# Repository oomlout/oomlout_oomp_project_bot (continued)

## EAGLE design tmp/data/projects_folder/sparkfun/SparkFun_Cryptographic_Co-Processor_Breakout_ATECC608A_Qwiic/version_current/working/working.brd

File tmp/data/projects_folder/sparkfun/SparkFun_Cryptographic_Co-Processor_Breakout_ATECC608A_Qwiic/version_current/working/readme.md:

# SparkFun_Cryptographic_Co-Processor_Breakout_ATECC608A_Qwiic by sparkfun  
This is a harvested standardized copy of a project from github.  
The original project can be found at:  
https://github.com/sparkfun/SparkFun_Cryptographic_Co-Processor_Breakout_ATECC608A_Qwiic  
Please consult that link for additional, details, files, and license information.  
Note: It was auto harvested and if the original repo had more than one board file or anything out of the ordinary the files here are likely not representative.

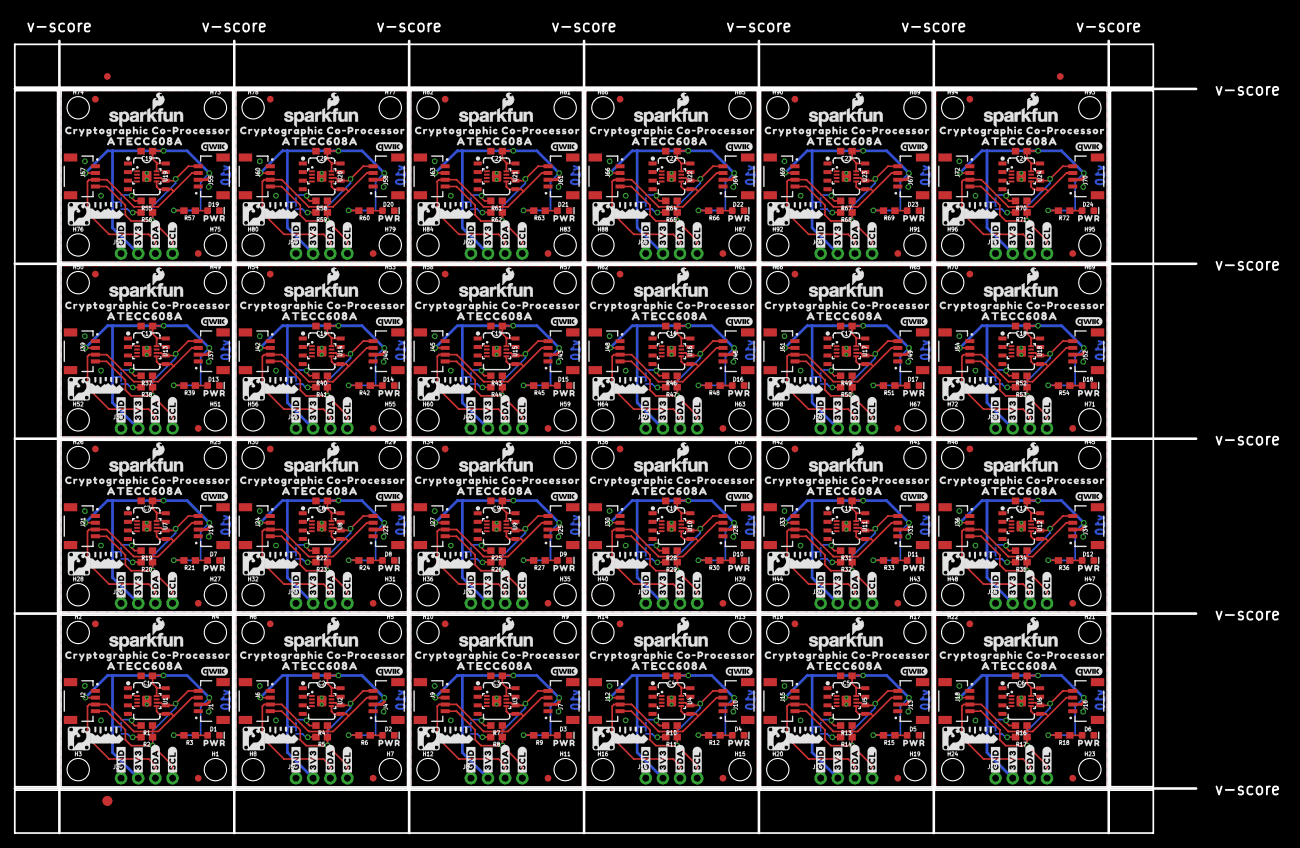
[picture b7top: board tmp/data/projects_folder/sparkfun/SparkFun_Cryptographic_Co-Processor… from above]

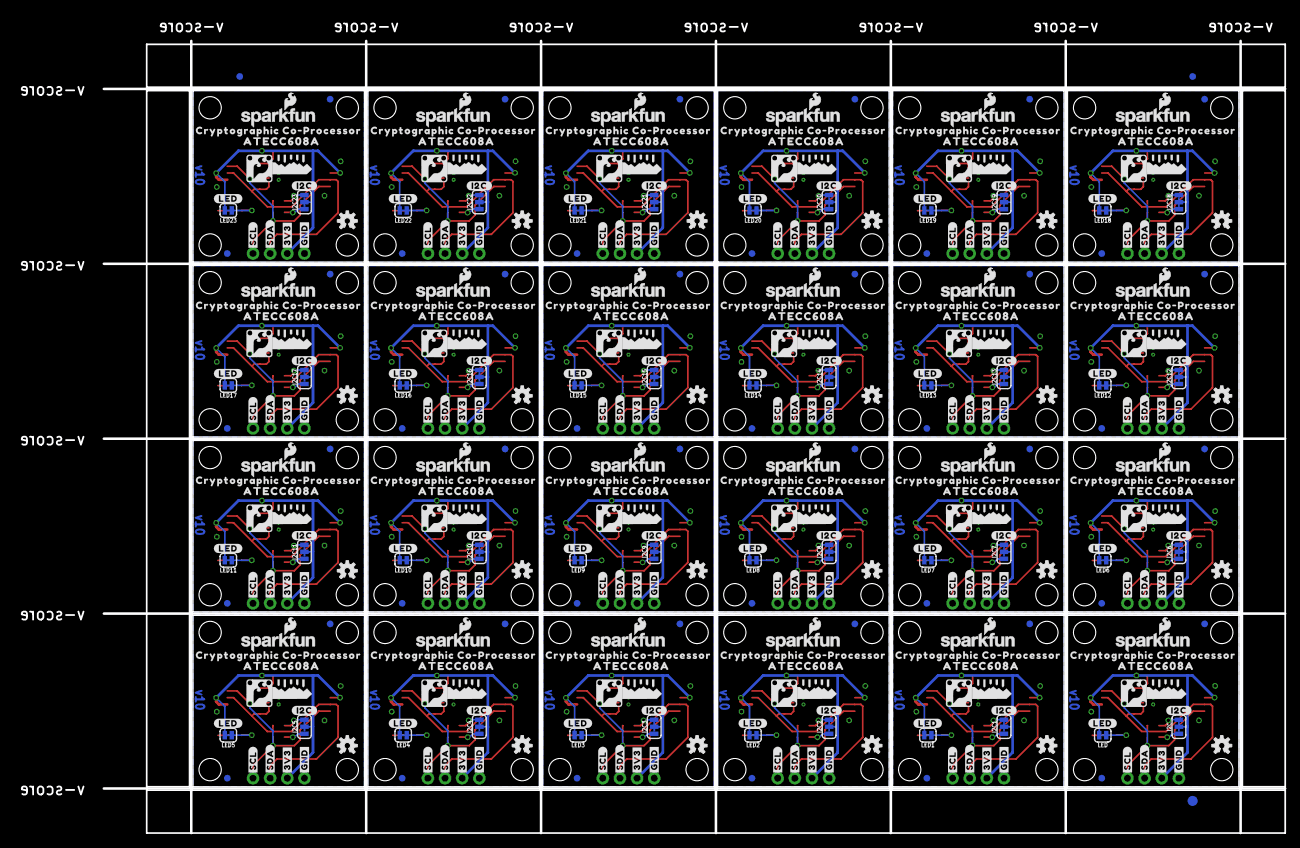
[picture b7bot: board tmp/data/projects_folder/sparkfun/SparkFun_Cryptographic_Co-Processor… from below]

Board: 2 copper layers, 175.0 x 117.3 mm, 966 parts (363 on the bottom side), 192 nets.

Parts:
C1, C2, C3, C4, C5, C6, C7, C8, C9, C10, C11, C12, C13, C14, C15, C16, C17, C18, C19, C20, C21, C22, C23, C24: 0.1uF; 0603
D1, D2, D3, D4, D5, D6, D7, D8, D9, D10, D11, D12, D13, D14, D15, D16, D17, D18, D19, D20, D21, D22, D23, D24: RED; LED-0603
E$1, E$2, E$3, E$4: FIDUCIAL-1X2
E$5, E$6: FIDUCIAL-1.5X3
FD1, FD2, FD3, FD4, FD5, FD6, FD7, FD8, FD9, FD10, FD11, FD12, FD13, FD14, FD15, FD16, FD17, FD18, FD19, FD20, FD21, FD22, FD23, FD24, FD25, FD26, FD27, FD28, FD29, FD30, FD31, FD32, FD33, FD34, FD35, FD36, FD37, FD38, FD39, FD40, FD41, FD42, FD43, FD44, FD45, FD46, FD47, FD48, FD49, FD50, FD51, FD52, FD53, FD54, FD55, FD56, FD57, FD58, FD59, FD60, FD61, FD62, FD63, FD64, FD65, FD66, FD67, FD68, FD69, FD70, FD71, FD72, FD73, FD74, FD75, FD76, FD77, FD78, FD79, FD80, FD81, FD82, FD83, FD84, FD85, FD86, FD87, FD88, FD89, FD90, FD91, FD92, FD93, FD94, FD95, FD96: FIDUCIAL1X2; FIDUCIAL-1X2
H1, H2, H3, H4, H5, H6, H7, H8, H9, H10, H11, H12, H13, H14, H15, H16, H17, H18, H19, H20, H21, H22, H23, H24, H25, H26, H27, H28, H29, H30, H31, H32, H33, H34, H35, H36, H37, H38, H39, H40, H41, H42, H43, H44, H45, H46, H47, H48, H49, H50, H51, H52, H53, H54, H55, H56, H57, H58, H59, H60, H61, H62, H63, H64, H65, H66, H67, H68, H69, H70, H71, H72, H73, H74, H75, H76, H77, H78, H79, H80, H81, H82, H83, H84, H85, H86, H87, H88, H89, H90, H91, H92, H93, H94, H95, H96: STAND-OFF
I2C, I2C1, I2C2, I2C3, I2C4, I2C5, I2C6, I2C7, I2C8, I2C9, I2C10, I2C11, I2C12, I2C13, I2C14, I2C15, I2C16, I2C17, I2C18, I2C19, I2C20, I2C21, I2C22, I2C23: SMT-JUMPER_3_2-NC_TRACE_SILK
J1, J2, J4, J6, J7, J9, J10, J12, J13, J15, J16, J18, J19, J21, J22, J24, J25, J27, J28, J30, J31, J33, J34, J36, J37, J39, J40, J42, J43, J45, J46, J48, J49, J51, J52, J54, J55, J57, J58, J60, J61, J63, J64, J66, J67, J69, J70, J72: QWIIC; JST04_1MM_RA
J3, J5, J8, J11, J14, J17, J20, J23, J26, J29, J32, J35, J38, J41, J44, J47, J50, J53, J56, J59, J62, J65, J68, J71: PTH; 1X04_NO_SILK
LED, LED1, LED2, LED3, LED4, LED5, LED6, LED7, LED8, LED9, LED10, LED11, LED12, LED13, LED14, LED15, LED16, LED17, LED18, LED19, LED20, LED21, LED22, LED23: SMT-JUMPER_2_NC_TRACE_SILK
LOGO1, LOGO2, LOGO6, LOGO7, LOGO10, LOGO11, LOGO14, LOGO15, LOGO18, LOGO19, LOGO22, LOGO23, LOGO26, LOGO27, LOGO30, LOGO31, LOGO34, LOGO35, LOGO38, LOGO39, LOGO42, LOGO43, LOGO46, LOGO47, LOGO50, LOGO51, LOGO54, LOGO55, LOGO58, LOGO59, LOGO62, LOGO63, LOGO66, LOGO67, LOGO70, LOGO71, LOGO74, LOGO75, LOGO78, LOGO79, LOGO82, LOGO83, LOGO86, LOGO87, LOGO90, LOGO91, LOGO94, LOGO95: SFE_LOGO_NAME_FLAME.1_INCH; SFE_LOGO_NAME_FLAME_.1
LOGO3, LOGO8, LOGO12, LOGO16, LOGO20, LOGO24, LOGO28, LOGO32, LOGO36, LOGO40, LOGO44, LOGO48, LOGO52, LOGO56, LOGO60, LOGO64, LOGO68, LOGO72, LOGO76, LOGO80, LOGO84, LOGO88, LOGO92, LOGO96: QWIIC_LOGO_4MM; QWIIC_4MM
LOGO4, LOGO5, LOGO9, LOGO13, LOGO17, LOGO21, LOGO25, LOGO29, LOGO33, LOGO37, LOGO41, LOGO45, LOGO49, LOGO53, LOGO57, LOGO61, LOGO65, LOGO69, LOGO73, LOGO77, LOGO81, LOGO85, LOGO89, LOGO93: OSHW-LOGOS; OSHW-LOGO-S
R1, R2, R4, R5, R7, R8, R10, R11, R13, R14, R16, R17, R19, R20, R22, R23, R25, R26, R28, R29, R31, R32, R34, R35, R37, R38, R40, R41, R43, R44, R46, R47, R49, R50, R52, R53, R55, R56, R58, R59, R61, R62, R64, R65, R67, R68, R70, R71: 4.7k; 0603
R3, R6, R9, R12, R15, R18, R21, R24, R27, R30, R33, R36, R39, R42, R45, R48, R51, R54, R57, R60, R63, R66, R69, R72: 1k; 0603
U1, U2, U3, U4, U5, U6, U7, U8, U9, U10, U11, U12, U13, U14, U15, U16, U17, U18, U19, U20, U21, U22, U23, U24: ATECC608A; DUAL_UDFN_2X3MM_SOIC-8
U$1, U$29, U$46, U$63, U$80, U$97, U$114, U$131, U$148, U$165, U$182, U$199, U$216, U$233, U$250, U$267, U$284, U$301, U$318, U$335, U$352, U$369, U$386, U$403: #I2C#0
U$2, U$13, U$15, U$24, U$37, U$41, U$54, U$58, U$71, U$75, U$88, U$92, U$105, U$109, U$122, U$126, U$139, U$143, U$156, U$160, U$173, U$177, U$190, U$194, U$207, U$211, U$224, U$228, U$241, U$245, U$258, U$262, U$275, U$279, U$292, U$296, U$309, U$313, U$326, U$330, U$343, U$347, U$360, U$364, U$377, U$381, U$394, U$398: #SCL#0
U$3, U$28, U$45, U$62, U$79, U$96, U$113, U$130, U$147, U$164, U$181, U$198, U$215, U$232, U$249, U$266, U$283, U$300, U$317, U$334, U$351, U$368, U$385, U$402: #LED#0
U$4, U$16, U$17, U$25, U$38, U$42, U$55, U$59, U$72, U$76, U$89, U$93, U$106, U$110, U$123, U$127, U$140, U$144, U$157, U$161, U$174, U$178, U$191, U$195, U$208, U$212, U$225, U$229, U$242, U$246, U$259, U$263, U$276, U$280, U$293, U$297, U$310, U$314, U$327, U$331, U$344, U$348, U$361, U$365, U$378, U$382, U$395, U$399: #SDA#0
U$5, U$7, U$30, U$31, U$47, U$48, U$64, U$65, U$81, U$82, U$98, U$99, U$115, U$116, U$132, U$133, U$149, U$150, U$166, U$167, U$183, U$184, U$200, U$201, U$217, U$218, U$234, U$235, U$251, U$252, U$268, U$269, U$285, U$286, U$302, U$303, U$319, U$320, U$336, U$337, U$353, U$354, U$370, U$371, U$387, U$388, U$404, U$405: ATECC608A0
U$6, U$18, U$20, U$26, U$39, U$43, U$56, U$60, U$73, U$77, U$90, U$94, U$107, U$111, U$124, U$128, U$141, U$145, U$158, U$162, U$175, U$179, U$192, U$196, U$209, U$213, U$226, U$230, U$243, U$247, U$260, U$264, U$277, U$281, U$294, U$298, U$311, U$315, U$328, U$332, U$345, U$349, U$362, U$366, U$379, U$383, U$396, U$400: #3V3#0
U$8, U$32, U$49, U$66, U$83, U$100, U$117, U$134, U$151, U$168, U$185, U$202, U$219, U$236, U$253, U$270, U$287, U$304, U$321, U$338, U$355, U$372, U$389, U$406: CRYPTO_COPROCESSOR_LOGO_LARGE
U$9, U$12, U$14, U$19, U$35, U$36, U$52, U$53, U$69, U$70, U$86, U$87, U$103, U$104, U$120, U$121, U$137, U$138, U$154, U$155, U$171, U$172, U$188, U$189, U$205, U$206, U$222, U$223, U$239, U$240, U$256, U$257, U$273, U$274, U$290, U$291, U$307, U$308, U$324, U$325, U$341, U$342, U$358, U$359, U$375, U$376, U$392, U$393: CRYPTOGRAPHIC_CO#PROCESSOR0
U$10, U$33, U$50, U$67, U$84, U$101, U$118, U$135, U$152, U$169, U$186, U$203, U$220, U$237, U$254, U$271, U$288, U$305, U$322, U$339, U$356, U$373, U$390, U$407: CRYPTO_COPROCESSOR_LOGO_SMALL
U$11, U$34, U$51, U$68, U$85, U$102, U$119, U$136, U$153, U$170, U$187, U$204, U$221, U$238, U$255, U$272, U$289, U$306, U$323, U$340, U$357, U$374, U$391, U$408: PWR0
U$21, U$22, U$23, U$27, U$40, U$44, U$57, U$61, U$74, U$78, U$91, U$95, U$108, U$112, U$125, U$129, U$142, U$146, U$159, U$163, U$176, U$180, U$193, U$197, U$210, U$214, U$227, U$231, U$244, U$248, U$261, U$265, U$278, U$282, U$295, U$299, U$312, U$316, U$329, U$333, U$346, U$350, U$363, U$367, U$380, U$384, U$397, U$401: #GND#0

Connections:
3.3V: C1.1, I2C.2, J1.2, J2.2, J3.2, LED.2, U1.8, U1.8S
3.3V1: C2.1, I2C1.2, J4.2, J5.2, J6.2, LED1.2, U2.8, U2.8S
3.3V2: C3.1, I2C2.2, J7.2, J8.2, J9.2, LED2.2, U3.8, U3.8S
3.3V3: C4.1, I2C3.2, J10.2, J11.2, J12.2, LED3.2, U4.8, U4.8S
3.3V4: C5.1, I2C4.2, J13.2, J14.2, J15.2, LED4.2, U5.8, U5.8S
3.3V5: C6.1, I2C5.2, J16.2, J17.2, J18.2, LED5.2, U6.8, U6.8S
3.3V6: C7.1, I2C6.2, J19.2, J20.2, J21.2, LED6.2, U7.8, U7.8S
3.3V7: C8.1, I2C7.2, J22.2, J23.2, J24.2, LED7.2, U8.8, U8.8S
3.3V8: C9.1, I2C8.2, J25.2, J26.2, J27.2, LED8.2, U9.8, U9.8S
3.3V9: C10.1, I2C9.2, J28.2, J29.2, J30.2, LED9.2, U10.8, U10.8S
3.3V10: C11.1, I2C10.2, J31.2, J32.2, J33.2, LED10.2, U11.8, U11.8S
3.3V11: C12.1, I2C11.2, J34.2, J35.2, J36.2, LED11.2, U12.8, U12.8S
3.3V12: C13.1, I2C12.2, J37.2, J38.2, J39.2, LED12.2, U13.8, U13.8S
3.3V13: C14.1, I2C13.2, J40.2, J41.2, J42.2, LED13.2, U14.8, U14.8S
3.3V14: C15.1, I2C14.2, J43.2, J44.2, J45.2, LED14.2, U15.8, U15.8S
3.3V15: C16.1, I2C15.2, J46.2, J47.2, J48.2, LED15.2, U16.8, U16.8S
3.3V16: C17.1, I2C16.2, J49.2, J50.2, J51.2, LED16.2, U17.8, U17.8S
3.3V17: C18.1, I2C17.2, J52.2, J53.2, J54.2, LED17.2, U18.8, U18.8S
3.3V18: C19.1, I2C18.2, J55.2, J56.2, J57.2, LED18.2, U19.8, U19.8S
3.3V19: C20.1, I2C19.2, J58.2, J59.2, J60.2, LED19.2, U20.8, U20.8S
3.3V20: C21.1, I2C20.2, J61.2, J62.2, J63.2, LED20.2, U21.8, U21.8S
3.3V21: C22.1, I2C21.2, J64.2, J65.2, J66.2, LED21.2, U22.8, U22.8S
3.3V22: C23.1, I2C22.2, J67.2, J68.2, J69.2, LED22.2, U23.8, U23.8S
3.3V23: C24.1, I2C23.2, J70.2, J71.2, J72.2, LED23.2, U24.8, U24.8S
GND: C1.2, D1.C, J1.1, J2.1, J3.1, U1.4, U1.4S, U1.P
GND1: C2.2, D2.C, J4.1, J5.1, J6.1, U2.4, U2.4S, U2.P
GND2: C3.2, D3.C, J7.1, J8.1, J9.1, U3.4, U3.4S, U3.P
GND3: C4.2, D4.C, J10.1, J11.1, J12.1, U4.4, U4.4S, U4.P
GND4: C5.2, D5.C, J13.1, J14.1, J15.1, U5.4, U5.4S, U5.P
GND5: C6.2, D6.C, J16.1, J17.1, J18.1, U6.4, U6.4S, U6.P
GND6: C7.2, D7.C, J19.1, J20.1, J21.1, U7.4, U7.4S, U7.P
GND7: C8.2, D8.C, J22.1, J23.1, J24.1, U8.4, U8.4S, U8.P
GND8: C9.2, D9.C, J25.1, J26.1, J27.1, U9.4, U9.4S, U9.P
GND9: C10.2, D10.C, J28.1, J29.1, J30.1, U10.4, U10.4S, U10.P
GND10: C11.2, D11.C, J31.1, J32.1, J33.1, U11.4, U11.4S, U11.P
GND11: C12.2, D12.C, J34.1, J35.1, J36.1, U12.4, U12.4S, U12.P
GND12: C13.2, D13.C, J37.1, J38.1, J39.1, U13.4, U13.4S, U13.P
GND13: C14.2, D14.C, J40.1, J41.1, J42.1, U14.4, U14.4S, U14.P
GND14: C15.2, D15.C, J43.1, J44.1, J45.1, U15.4, U15.4S, U15.P
GND15: C16.2, D16.C, J46.1, J47.1, J48.1, U16.4, U16.4S, U16.P
GND16: C17.2, D17.C, J49.1, J50.1, J51.1, U17.4, U17.4S, U17.P
GND17: C18.2, D18.C, J52.1, J53.1, J54.1, U18.4, U18.4S, U18.P
GND18: C19.2, D19.C, J55.1, J56.1, J57.1, U19.4, U19.4S, U19.P
GND19: C20.2, D20.C, J58.1, J59.1, J60.1, U20.4, U20.4S, U20.P
GND20: C21.2, D21.C, J61.1, J62.1, J63.1, U21.4, U21.4S, U21.P
GND21: C22.2, D22.C, J64.1, J65.1, J66.1, U22.4, U22.4S, U22.P
GND22: C23.2, D23.C, J67.1, J68.1, J69.1, U23.4, U23.4S, U23.P
GND23: C24.2, D24.C, J70.1, J71.1, J72.1, U24.4, U24.4S, U24.P
unnamed: I2C1.3, R4.2
unnamed: I2C1.1, R5.2
unnamed: D1.A, R3.1
unnamed: I2C.3, R1.2
unnamed: I2C.1, R2.2
unnamed: D2.A, R6.1
unnamed: LED.1, R3.2
unnamed: LED1.1, R6.2
unnamed: I2C2.3, R7.2
unnamed: I2C2.1, R8.2
unnamed: D3.A, R9.1
unnamed: LED2.1, R9.2
unnamed: I2C3.3, R10.2
unnamed: I2C3.1, R11.2
unnamed: D4.A, R12.1
unnamed: LED3.1, R12.2
unnamed: I2C4.3, R13.2
unnamed: I2C4.1, R14.2
unnamed: D5.A, R15.1
unnamed: LED4.1, R15.2
unnamed: I2C5.3, R16.2
unnamed: I2C5.1, R17.2
unnamed: D6.A, R18.1
unnamed: LED5.1, R18.2
unnamed: I2C6.3, R19.2
unnamed: I2C6.1, R20.2
unnamed: D7.A, R21.1
unnamed: LED6.1, R21.2
unnamed: I2C7.3, R22.2
unnamed: I2C7.1, R23.2
unnamed: D8.A, R24.1
unnamed: LED7.1, R24.2
unnamed: I2C8.3, R25.2
unnamed: I2C8.1, R26.2
unnamed: D9.A, R27.1
unnamed: LED8.1, R27.2
unnamed: I2C9.3, R28.2
unnamed: I2C9.1, R29.2
unnamed: D10.A, R30.1
unnamed: LED9.1, R30.2
unnamed: I2C10.3, R31.2
unnamed: I2C10.1, R32.2
unnamed: D11.A, R33.1
unnamed: LED10.1, R33.2
unnamed: I2C11.3, R34.2
unnamed: I2C11.1, R35.2
unnamed: D12.A, R36.1
unnamed: LED11.1, R36.2
unnamed: I2C12.3, R37.2
unnamed: I2C12.1, R38.2
unnamed: D13.A, R39.1
unnamed: LED12.1, R39.2
unnamed: I2C13.3, R40.2
unnamed: I2C13.1, R41.2
unnamed: D14.A, R42.1
unnamed: LED13.1, R42.2
unnamed: I2C14.3, R43.2
unnamed: I2C14.1, R44.2
unnamed: D15.A, R45.1
unnamed: LED14.1, R45.2
unnamed: I2C15.3, R46.2
unnamed: I2C15.1, R47.2
unnamed: D16.A, R48.1
unnamed: LED15.1, R48.2
unnamed: I2C16.3, R49.2
unnamed: I2C16.1, R50.2
unnamed: D17.A, R51.1
unnamed: LED16.1, R51.2
unnamed: I2C17.3, R52.2
unnamed: I2C17.1, R53.2
unnamed: D18.A, R54.1
unnamed: LED17.1, R54.2
unnamed: I2C18.3, R55.2
unnamed: I2C18.1, R56.2
unnamed: D19.A, R57.1
unnamed: LED18.1, R57.2
unnamed: I2C19.3, R58.2
unnamed: I2C19.1, R59.2
unnamed: D20.A, R60.1
unnamed: LED19.1, R60.2
unnamed: I2C20.3, R61.2
unnamed: I2C20.1, R62.2
unnamed: D21.A, R63.1
unnamed: LED20.1, R63.2
unnamed: I2C21.3, R64.2
unnamed: I2C21.1, R65.2
unnamed: D22.A, R66.1
unnamed: LED21.1, R66.2
unnamed: I2C22.3, R67.2
unnamed: I2C22.1, R68.2
unnamed: D23.A, R69.1
unnamed: LED22.1, R69.2
unnamed: I2C23.3, R70.2
unnamed: I2C23.1, R71.2
unnamed: D24.A, R72.1
unnamed: LED23.1, R72.2
SCL: J1.4, J2.4, J3.4, R2.1, U1.6, U1.6S
SCL1: J4.4, J5.4, J6.4, R5.1, U2.6, U2.6S
SCL2: J7.4, J8.4, J9.4, R8.1, U3.6, U3.6S
SCL3: J10.4, J11.4, J12.4, R11.1, U4.6, U4.6S
SCL4: J13.4, J14.4, J15.4, R14.1, U5.6, U5.6S
SCL5: J16.4, J17.4, J18.4, R17.1, U6.6, U6.6S
SCL6: J19.4, J20.4, J21.4, R20.1, U7.6, U7.6S
SCL7: J22.4, J23.4, J24.4, R23.1, U8.6, U8.6S
SCL8: J25.4, J26.4, J27.4, R26.1, U9.6, U9.6S
SCL9: J28.4, J29.4, J30.4, R29.1, U10.6, U10.6S
SCL10: J31.4, J32.4, J33.4, R32.1, U11.6, U11.6S
SCL11: J34.4, J35.4, J36.4, R35.1, U12.6, U12.6S
SCL12: J37.4, J38.4, J39.4, R38.1, U13.6, U13.6S
SCL13: J40.4, J41.4, J42.4, R41.1, U14.6, U14.6S
SCL14: J43.4, J44.4, J45.4, R44.1, U15.6, U15.6S
SCL15: J46.4, J47.4, J48.4, R47.1, U16.6, U16.6S
SCL16: J49.4, J50.4, J51.4, R50.1, U17.6, U17.6S
SCL17: J52.4, J53.4, J54.4, R53.1, U18.6, U18.6S
SCL18: J55.4, J56.4, J57.4, R56.1, U19.6, U19.6S
SCL19: J58.4, J59.4, J60.4, R59.1, U20.6, U20.6S
SCL20: J61.4, J62.4, J63.4, R62.1, U21.6, U21.6S
SCL21: J64.4, J65.4, J66.4, R65.1, U22.6, U22.6S
SCL22: J67.4, J68.4, J69.4, R68.1, U23.6, U23.6S
SCL23: J70.4, J71.4, J72.4, R71.1, U24.6, U24.6S
SDA: J1.3, J2.3, J3.3, R1.1, U1.5, U1.5S
SDA1: J4.3, J5.3, J6.3, R4.1, U2.5, U2.5S
SDA2: J7.3, J8.3, J9.3, R7.1, U3.5, U3.5S
SDA3: J10.3, J11.3, J12.3, R10.1, U4.5, U4.5S
SDA4: J13.3, J14.3, J15.3, R13.1, U5.5, U5.5S
SDA5: J16.3, J17.3, J18.3, R16.1, U6.5, U6.5S
SDA6: J19.3, J20.3, J21.3, R19.1, U7.5, U7.5S
SDA7: J22.3, J23.3, J24.3, R22.1, U8.5, U8.5S
SDA8: J25.3, J26.3, J27.3, R25.1, U9.5, U9.5S
SDA9: J28.3, J29.3, J30.3, R28.1, U10.5, U10.5S
SDA10: J31.3, J32.3, J33.3, R31.1, U11.5, U11.5S
SDA11: J34.3, J35.3, J36.3, R34.1, U12.5, U12.5S
SDA12: J37.3, J38.3, J39.3, R37.1, U13.5, U13.5S
SDA13: J40.3, J41.3, J42.3, R40.1, U14.5, U14.5S
SDA14: J43.3, J44.3, J45.3, R43.1, U15.5, U15.5S
SDA15: J46.3, J47.3, J48.3, R46.1, U16.5, U16.5S
SDA16: J49.3, J50.3, J51.3, R49.1, U17.5, U17.5S
SDA17: J52.3, J53.3, J54.3, R52.1, U18.5, U18.5S
SDA18: J55.3, J56.3, J57.3, R55.1, U19.5, U19.5S
SDA19: J58.3, J59.3, J60.3, R58.1, U20.5, U20.5S
SDA20: J61.3, J62.3, J63.3, R61.1, U21.5, U21.5S
SDA21: J64.3, J65.3, J66.3, R64.1, U22.5, U22.5S
SDA22: J67.3, J68.3, J69.3, R67.1, U23.5, U23.5S
SDA23: J70.3, J71.3, J72.3, R70.1, U24.5, U24.5S

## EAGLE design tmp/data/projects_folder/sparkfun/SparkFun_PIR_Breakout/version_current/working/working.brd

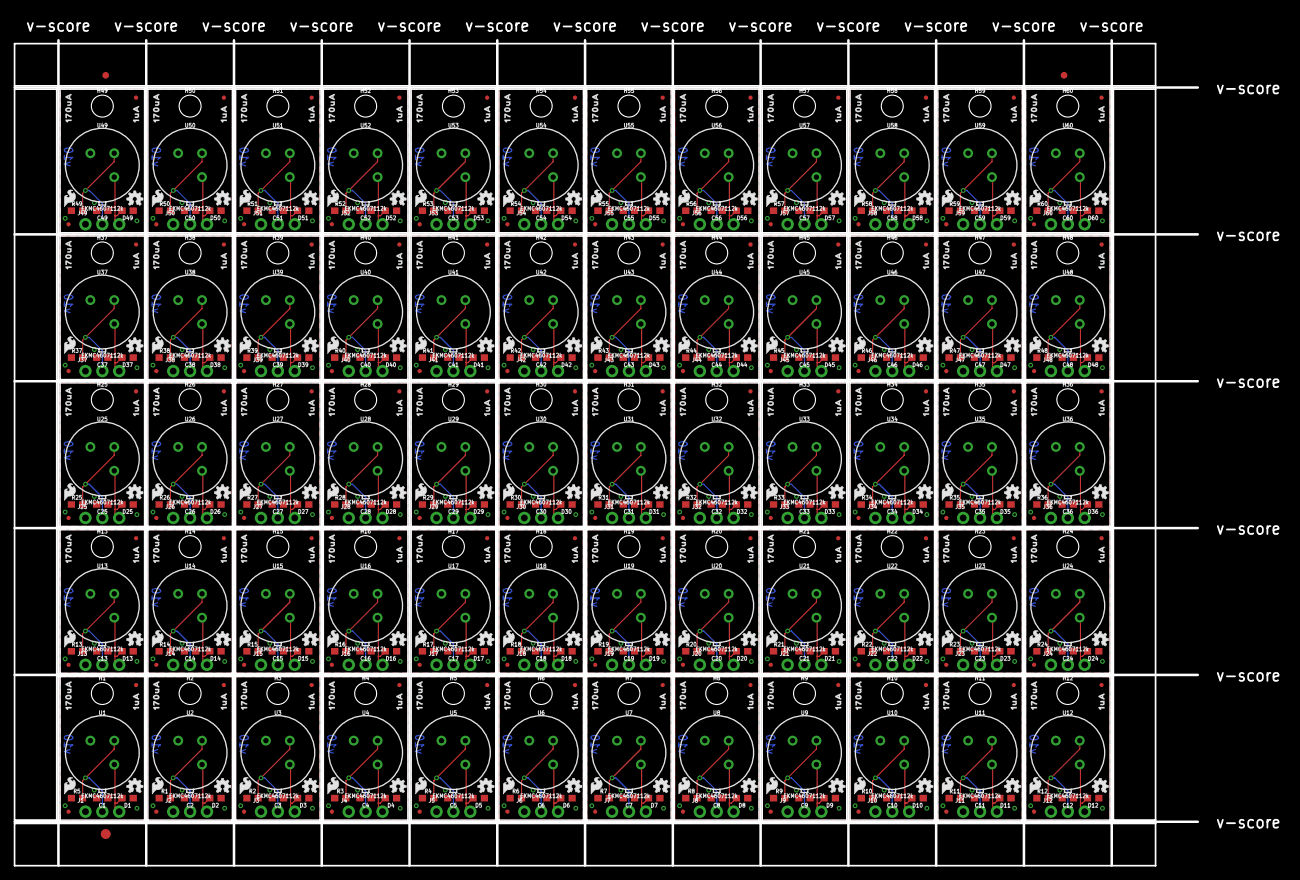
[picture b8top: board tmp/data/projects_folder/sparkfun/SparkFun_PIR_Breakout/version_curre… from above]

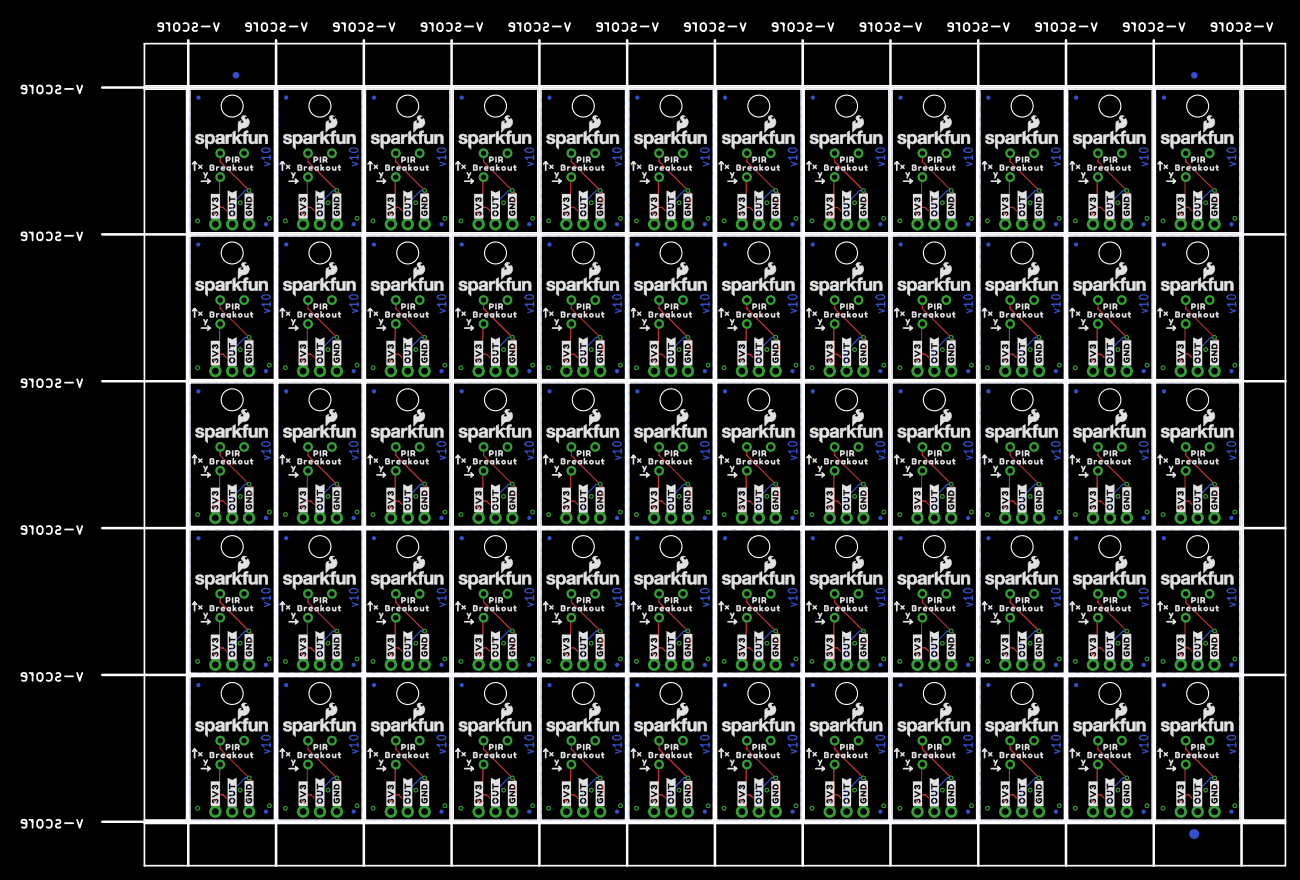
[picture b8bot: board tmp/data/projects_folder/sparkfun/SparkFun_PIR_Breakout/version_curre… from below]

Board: 2 copper layers, 178.1 x 124.2 mm, 1326 parts (603 on the bottom side), 180 nets.

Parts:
C1, C2, C3, C4, C5, C6, C7, C8, C9, C10, C11, C12, C13, C14, C15, C16, C17, C18, C19, C20, C21, C22, C23, C24, C25, C26, C27, C28, C29, C30, C31, C32, C33, C34, C35, C36, C37, C38, C39, C40, C41, C42, C43, C44, C45, C46, C47, C48, C49, C50, C51, C52, C53, C54, C55, C56, C57, C58, C59, C60: 0.1uF; 0603
D1, D2, D3, D4, D5, D6, D7, D8, D9, D10, D11, D12, D13, D14, D15, D16, D17, D18, D19, D20, D21, D22, D23, D24, D25, D26, D27, D28, D29, D30, D31, D32, D33, D34, D35, D36, D37, D38, D39, D40, D41, D42, D43, D44, D45, D46, D47, D48, D49, D50, D51, D52, D53, D54, D55, D56, D57, D58, D59, D60: 24V; 0603
E$1, E$2, E$3, E$4: FIDUCIAL-1X2
E$5, E$6: FIDUCIAL-1.5X3
H1, H2, H3, H4, H5, H6, H7, H8, H9, H10, H11, H12, H13, H14, H15, H16, H17, H18, H19, H20, H21, H22, H23, H24, H25, H26, H27, H28, H29, H30, H31, H32, H33, H34, H35, H36, H37, H38, H39, H40, H41, H42, H43, H44, H45, H46, H47, H48, H49, H50, H51, H52, H53, H54, H55, H56, H57, H58, H59, H60: STAND-OFF
J1, J2, J3, J4, J5, J6, J7, J8, J9, J10, J11, J12, J13, J14, J15, J16, J17, J18, J19, J20, J21, J22, J23, J24, J25, J26, J27, J28, J29, J30, J31, J32, J33, J34, J35, J36, J37, J38, J39, J40, J41, J42, J43, J44, J45, J46, J47, J48, J49, J50, J51, J52, J53, J54, J55, J56, J57, J58, J59, J60: 1X03_NO_SILK
JP1, JP2, JP3, JP4, JP5, JP6, JP7, JP8, JP9, JP10, JP11, JP12, JP13, JP14, JP15, JP16, JP17, JP18, JP19, JP20, JP21, JP22, JP23, JP24, JP25, JP26, JP27, JP28, JP29, JP30, JP31, JP32, JP33, JP34, JP35, JP36, JP37, JP38, JP39, JP40, JP41, JP42, JP43, JP44, JP45, JP46, JP47, JP48, JP49, JP50, JP51, JP52, JP53, JP54, JP55, JP56, JP57, JP58, JP59, JP60, JP61, JP62, JP63, JP64, JP65, JP66, JP67, JP68, JP69, JP70, JP71, JP72, JP73, JP74, JP75, JP76, JP77, JP78, JP79, JP80, JP81, JP82, JP83, JP84, JP85, JP86, JP87, JP88, JP89, JP90, JP91, JP92, JP93, JP94, JP95, JP96, JP97, JP98, JP99, JP100, JP101, JP102, JP103, JP104, JP105, JP106, JP107, JP108, JP109, JP110, JP111, JP112, JP113, JP114, JP115, JP116, JP117, JP118, JP119, JP120, JP121, JP122, JP123, JP124, JP125, JP126, JP127, JP128, JP129, JP130, JP131, JP132, JP133, JP134, JP135, JP136, JP137, JP138, JP139, JP140, JP141, JP142, JP143, JP144, JP145, JP146, JP147, JP148, JP149, JP150, JP151, JP152, JP153, JP154, JP155, JP156, JP157, JP158, JP159, JP160, JP161, JP162, JP163, JP164, JP165, JP166, JP167, JP168, JP169, JP170, JP171, JP172, JP173, JP174, JP175, JP176, JP177, JP178, JP179, JP180, JP181, JP182, JP183, JP184, JP185, JP186, JP187, JP188, JP189, JP190, JP191, JP192, JP193, JP194, JP195, JP196, JP197, JP198, JP199, JP200, JP201, JP202, JP203, JP204, JP205, JP206, JP207, JP208, JP209, JP210, JP211, JP212, JP213, JP214, JP215, JP216, JP217, JP218, JP219, JP220, JP221, JP222, JP223, JP224, JP225, JP226, JP227, JP228, JP229, JP230, JP231, JP232, JP233, JP234, JP235, JP236, JP237, JP238, JP239, JP240: FIDUCIALUFIDUCIAL; MICRO-FIDUCIAL
LOGO1, LOGO2, LOGO7, LOGO10, LOGO13, LOGO16, LOGO19, LOGO22, LOGO25, LOGO28, LOGO31, LOGO34, LOGO37, LOGO40, LOGO43, LOGO46, LOGO49, LOGO52, LOGO55, LOGO58, LOGO61, LOGO64, LOGO67, LOGO70, LOGO73, LOGO76, LOGO79, LOGO82, LOGO85, LOGO88, LOGO91, LOGO94, LOGO97, LOGO100, LOGO103, LOGO106, LOGO109, LOGO112, LOGO115, LOGO118, LOGO121, LOGO124, LOGO127, LOGO130, LOGO133, LOGO136, LOGO139, LOGO142, LOGO145, LOGO148, LOGO151, LOGO154, LOGO157, LOGO160, LOGO163, LOGO166, LOGO169, LOGO172, LOGO175, LOGO178: OSHW-LOGOMINI; OSHW-LOGO-MINI
LOGO3, LOGO5, LOGO8, LOGO11, LOGO14, LOGO17, LOGO20, LOGO23, LOGO26, LOGO29, LOGO32, LOGO35, LOGO38, LOGO41, LOGO44, LOGO47, LOGO50, LOGO53, LOGO56, LOGO59, LOGO62, LOGO65, LOGO68, LOGO71, LOGO74, LOGO77, LOGO80, LOGO83, LOGO86, LOGO89, LOGO92, LOGO95, LOGO98, LOGO101, LOGO104, LOGO107, LOGO110, LOGO113, LOGO116, LOGO119, LOGO122, LOGO125, LOGO128, LOGO131, LOGO134, LOGO137, LOGO140, LOGO143, LOGO146, LOGO149, LOGO152, LOGO155, LOGO158, LOGO161, LOGO164, LOGO167, LOGO170, LOGO173, LOGO176, LOGO179: SFE_LOGO_NAME_FLAME.1_INCH; SFE_LOGO_NAME_FLAME_.1
LOGO4, LOGO6, LOGO9, LOGO12, LOGO15, LOGO18, LOGO21, LOGO24, LOGO27, LOGO30, LOGO33, LOGO36, LOGO39, LOGO42, LOGO45, LOGO48, LOGO51, LOGO54, LOGO57, LOGO60, LOGO63, LOGO66, LOGO69, LOGO72, LOGO75, LOGO78, LOGO81, LOGO84, LOGO87, LOGO90, LOGO93, LOGO96, LOGO99, LOGO102, LOGO105, LOGO108, LOGO111, LOGO114, LOGO117, LOGO120, LOGO123, LOGO126, LOGO129, LOGO132, LOGO135, LOGO138, LOGO141, LOGO144, LOGO147, LOGO150, LOGO153, LOGO156, LOGO159, LOGO162, LOGO165, LOGO168, LOGO171, LOGO174, LOGO177, LOGO180: SFE_LOGO_FLAME.1_INCH; SFE_LOGO_FLAME_.1
R1, R2, R3, R4, R5, R6, R7, R8, R9, R10, R11, R12, R13, R14, R15, R16, R17, R18, R19, R20, R21, R22, R23, R24, R25, R26, R27, R28, R29, R30, R31, R32, R33, R34, R35, R36, R37, R38, R39, R40, R41, R42, R43, R44, R45, R46, R47, R48, R49, R50, R51, R52, R53, R54, R55, R56, R57, R58, R59, R60: 47k; 0603
U1, U2, U3, U4, U5, U6, U7, U8, U9, U10, U11, U12, U13, U14, U15, U16, U17, U18, U19, U20, U21, U22, U23, U24, U25, U26, U27, U28, U29, U30, U31, U32, U33, U34, U35, U36, U37, U38, U39, U40, U41, U42, U43, U44, U45, U46, U47, U48, U49, U50, U51, U52, U53, U54, U55, U56, U57, U58, U59, U60: EKMC4607112k; TO-3
U$1, U$10, U$24, U$33, U$42, U$51, U$60, U$69, U$78, U$87, U$96, U$105, U$114, U$123, U$132, U$141, U$150, U$159, U$168, U$177, U$186, U$195, U$204, U$213, U$222, U$231, U$240, U$249, U$258, U$267, U$276, U$285, U$294, U$303, U$312, U$321, U$330, U$339, U$348, U$357, U$366, U$375, U$384, U$393, U$402, U$411, U$420, U$429, U$438, U$447, U$456, U$465, U$474, U$483, U$492, U$501, U$510, U$519, U$528, U$537: #3V3#0
U$2, U$5, U$20, U$29, U$38, U$47, U$56, U$65, U$74, U$83, U$92, U$101, U$110, U$119, U$128, U$137, U$146, U$155, U$164, U$173, U$182, U$191, U$200, U$209, U$218, U$227, U$236, U$245, U$254, U$263, U$272, U$281, U$290, U$299, U$308, U$317, U$326, U$335, U$344, U$353, U$362, U$371, U$380, U$389, U$398, U$407, U$416, U$425, U$434, U$443, U$452, U$461, U$470, U$479, U$488, U$497, U$506, U$515, U$524, U$533: 170UA0
U$3, U$15, U$25, U$34, U$43, U$52, U$61, U$70, U$79, U$88, U$97, U$106, U$115, U$124, U$133, U$142, U$151, U$160, U$169, U$178, U$187, U$196, U$205, U$214, U$223, U$232, U$241, U$250, U$259, U$268, U$277, U$286, U$295, U$304, U$313, U$322, U$331, U$340, U$349, U$358, U$367, U$376, U$385, U$394, U$403, U$412, U$421, U$430, U$439, U$448, U$457, U$466, U$475, U$484, U$493, U$502, U$511, U$520, U$529, U$538: #GND#0
U$4, U$13, U$19, U$28, U$37, U$46, U$55, U$64, U$73, U$82, U$91, U$100, U$109, U$118, U$127, U$136, U$145, U$154, U$163, U$172, U$181, U$190, U$199, U$208, U$217, U$226, U$235, U$244, U$253, U$262, U$271, U$280, U$289, U$298, U$307, U$316, U$325, U$334, U$343, U$352, U$361, U$370, U$379, U$388, U$397, U$406, U$415, U$424, U$433, U$442, U$451, U$460, U$469, U$478, U$487, U$496, U$505, U$514, U$523, U$532: PIR0
U$6, U$9, U$21, U$30, U$39, U$48, U$57, U$66, U$75, U$84, U$93, U$102, U$111, U$120, U$129, U$138, U$147, U$156, U$165, U$174, U$183, U$192, U$201, U$210, U$219, U$228, U$237, U$246, U$255, U$264, U$273, U$282, U$291, U$300, U$309, U$318, U$327, U$336, U$345, U$354, U$363, U$372, U$381, U$390, U$399, U$408, U$417, U$426, U$435, U$444, U$453, U$462, U$471, U$480, U$489, U$498, U$507, U$516, U$525, U$534: 1UA0
U$7, U$12, U$22, U$31, U$40, U$49, U$58, U$67, U$76, U$85, U$94, U$103, U$112, U$121, U$130, U$139, U$148, U$157, U$166, U$175, U$184, U$193, U$202, U$211, U$220, U$229, U$238, U$247, U$256, U$265, U$274, U$283, U$292, U$301, U$310, U$319, U$328, U$337, U$346, U$355, U$364, U$373, U$382, U$391, U$400, U$409, U$418, U$427, U$436, U$445, U$454, U$463, U$472, U$481, U$490, U$499, U$508, U$517, U$526, U$535: BREAKOUT0
U$8, U$11, U$23, U$32, U$41, U$50, U$59, U$68, U$77, U$86, U$95, U$104, U$113, U$122, U$131, U$140, U$149, U$158, U$167, U$176, U$185, U$194, U$203, U$212, U$221, U$230, U$239, U$248, U$257, U$266, U$275, U$284, U$293, U$302, U$311, U$320, U$329, U$338, U$347, U$356, U$365, U$374, U$383, U$392, U$401, U$410, U$419, U$428, U$437, U$446, U$455, U$464, U$473, U$482, U$491, U$500, U$509, U$518, U$527, U$536: #OUT#0
U$14, U$17, U$26, U$35, U$44, U$53, U$62, U$71, U$80, U$89, U$98, U$107, U$116, U$125, U$134, U$143, U$152, U$161, U$170, U$179, U$188, U$197, U$206, U$215, U$224, U$233, U$242, U$251, U$260, U$269, U$278, U$287, U$296, U$305, U$314, U$323, U$332, U$341, U$350, U$359, U$368, U$377, U$386, U$395, U$404, U$413, U$422, U$431, U$440, U$449, U$458, U$467, U$476, U$485, U$494, U$503, U$512, U$521, U$530, U$539: X0
U$16, U$18, U$27, U$36, U$45, U$54, U$63, U$72, U$81, U$90, U$99, U$108, U$117, U$126, U$135, U$144, U$153, U$162, U$171, U$180, U$189, U$198, U$207, U$216, U$225, U$234, U$243, U$252, U$261, U$270, U$279, U$288, U$297, U$306, U$315, U$324, U$333, U$342, U$351, U$360, U$369, U$378, U$387, U$396, U$405, U$414, U$423, U$432, U$441, U$450, U$459, U$468, U$477, U$486, U$495, U$504, U$513, U$522, U$531, U$540: Y0

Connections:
3.3V: C1.1, D1.2, J1.3, U1.VDD
3.3V1: C2.1, D2.2, J2.3, U2.VDD
3.3V2: C3.1, D3.2, J3.3, U3.VDD
3.3V3: C4.1, D4.2, J4.3, U4.VDD
3.3V4: C5.1, D5.2, J5.3, U5.VDD
3.3V5: C6.1, D6.2, J6.3, U6.VDD
3.3V6: C7.1, D7.2, J7.3, U7.VDD
3.3V7: C8.1, D8.2, J8.3, U8.VDD
3.3V8: C9.1, D9.2, J9.3, U9.VDD
3.3V9: C10.1, D10.2, J10.3, U10.VDD
3.3V10: C11.1, D11.2, J11.3, U11.VDD
3.3V11: C12.1, D12.2, J12.3, U12.VDD
3.3V12: C13.1, D13.2, J13.3, U13.VDD
3.3V13: C14.1, D14.2, J14.3, U14.VDD
3.3V14: C15.1, D15.2, J15.3, U15.VDD
3.3V15: C16.1, D16.2, J16.3, U16.VDD
3.3V16: C17.1, D17.2, J17.3, U17.VDD
3.3V17: C18.1, D18.2, J18.3, U18.VDD
3.3V18: C19.1, D19.2, J19.3, U19.VDD
3.3V19: C20.1, D20.2, J20.3, U20.VDD
3.3V20: C21.1, D21.2, J21.3, U21.VDD
3.3V21: C22.1, D22.2, J22.3, U22.VDD
3.3V22: C23.1, D23.2, J23.3, U23.VDD
3.3V23: C24.1, D24.2, J24.3, U24.VDD
3.3V24: C25.1, D25.2, J25.3, U25.VDD
3.3V25: C26.1, D26.2, J26.3, U26.VDD
3.3V26: C27.1, D27.2, J27.3, U27.VDD
3.3V27: C28.1, D28.2, J28.3, U28.VDD
3.3V28: C29.1, D29.2, J29.3, U29.VDD
3.3V29: C30.1, D30.2, J30.3, U30.VDD
3.3V30: C31.1, D31.2, J31.3, U31.VDD
3.3V31: C32.1, D32.2, J32.3, U32.VDD
3.3V32: C33.1, D33.2, J33.3, U33.VDD
3.3V33: C34.1, D34.2, J34.3, U34.VDD
3.3V34: C35.1, D35.2, J35.3, U35.VDD
3.3V35: C36.1, D36.2, J36.3, U36.VDD
3.3V36: C37.1, D37.2, J37.3, U37.VDD
3.3V37: C38.1, D38.2, J38.3, U38.VDD
3.3V38: C39.1, D39.2, J39.3, U39.VDD
3.3V39: C40.1, D40.2, J40.3, U40.VDD
3.3V40: C41.1, D41.2, J41.3, U41.VDD
3.3V41: C42.1, D42.2, J42.3, U42.VDD
3.3V42: C43.1, D43.2, J43.3, U43.VDD
3.3V43: C44.1, D44.2, J44.3, U44.VDD
3.3V44: C45.1, D45.2, J45.3, U45.VDD
3.3V45: C46.1, D46.2, J46.3, U46.VDD
3.3V46: C47.1, D47.2, J47.3, U47.VDD
3.3V47: C48.1, D48.2, J48.3, U48.VDD
3.3V48: C49.1, D49.2, J49.3, U49.VDD
3.3V49: C50.1, D50.2, J50.3, U50.VDD
3.3V50: C51.1, D51.2, J51.3, U51.VDD
3.3V51: C52.1, D52.2, J52.3, U52.VDD
3.3V52: C53.1, D53.2, J53.3, U53.VDD
3.3V53: C54.1, D54.2, J54.3, U54.VDD
3.3V54: C55.1, D55.2, J55.3, U55.VDD
3.3V55: C56.1, D56.2, J56.3, U56.VDD
3.3V56: C57.1, D57.2, J57.3, U57.VDD
3.3V57: C58.1, D58.2, J58.3, U58.VDD
3.3V58: C59.1, D59.2, J59.3, U59.VDD
3.3V59: C60.1, D60.2, J60.3, U60.VDD
GND: C1.2, D1.1, J1.1, R5.1, U1.GND
GND1: C2.2, D2.1, J2.1, R1.1, U2.GND
GND2: C3.2, D3.1, J3.1, R2.1, U3.GND
GND3: C4.2, D4.1, J4.1, R3.1, U4.GND
GND4: C5.2, D5.1, J5.1, R4.1, U5.GND
GND5: C6.2, D6.1, J6.1, R6.1, U6.GND
GND6: C7.2, D7.1, J7.1, R7.1, U7.GND
GND7: C8.2, D8.1, J8.1, R8.1, U8.GND
GND8: C9.2, D9.1, J9.1, R9.1, U9.GND
GND9: C10.2, D10.1, J10.1, R10.1, U10.GND
GND10: C11.2, D11.1, J11.1, R11.1, U11.GND
GND11: C12.2, D12.1, J12.1, R12.1, U12.GND
GND12: C13.2, D13.1, J13.1, R13.1, U13.GND
GND13: C14.2, D14.1, J14.1, R14.1, U14.GND
GND14: C15.2, D15.1, J15.1, R15.1, U15.GND
GND15: C16.2, D16.1, J16.1, R16.1, U16.GND
GND16: C17.2, D17.1, J17.1, R17.1, U17.GND
GND17: C18.2, D18.1, J18.1, R18.1, U18.GND
GND18: C19.2, D19.1, J19.1, R19.1, U19.GND
GND19: C20.2, D20.1, J20.1, R20.1, U20.GND
GND20: C21.2, D21.1, J21.1, R21.1, U21.GND
GND21: C22.2, D22.1, J22.1, R22.1, U22.GND
GND22: C23.2, D23.1, J23.1, R23.1, U23.GND
GND23: C24.2, D24.1, J24.1, R24.1, U24.GND
GND24: C25.2, D25.1, J25.1, R25.1, U25.GND
GND25: C26.2, D26.1, J26.1, R26.1, U26.GND
GND26: C27.2, D27.1, J27.1, R27.1, U27.GND
GND27: C28.2, D28.1, J28.1, R28.1, U28.GND
GND28: C29.2, D29.1, J29.1, R29.1, U29.GND
GND29: C30.2, D30.1, J30.1, R30.1, U30.GND
GND30: C31.2, D31.1, J31.1, R31.1, U31.GND
GND31: C32.2, D32.1, J32.1, R32.1, U32.GND
GND32: C33.2, D33.1, J33.1, R33.1, U33.GND
GND33: C34.2, D34.1, J34.1, R34.1, U34.GND
GND34: C35.2, D35.1, J35.1, R35.1, U35.GND
GND35: C36.2, D36.1, J36.1, R36.1, U36.GND
GND36: C37.2, D37.1, J37.1, R37.1, U37.GND
GND37: C38.2, D38.1, J38.1, R38.1, U38.GND
GND38: C39.2, D39.1, J39.1, R39.1, U39.GND
GND39: C40.2, D40.1, J40.1, R40.1, U40.GND
GND40: C41.2, D41.1, J41.1, R41.1, U41.GND
GND41: C42.2, D42.1, J42.1, R42.1, U42.GND
GND42: C43.2, D43.1, J43.1, R43.1, U43.GND
GND43: C44.2, D44.1, J44.1, R44.1, U44.GND
GND44: C45.2, D45.1, J45.1, R45.1, U45.GND
GND45: C46.2, D46.1, J46.1, R46.1, U46.GND
GND46: C47.2, D47.1, J47.1, R47.1, U47.GND
GND47: C48.2, D48.1, J48.1, R48.1, U48.GND
GND48: C49.2, D49.1, J49.1, R49.1, U49.GND
GND49: C50.2, D50.1, J50.1, R50.1, U50.GND
GND50: C51.2, D51.1, J51.1, R51.1, U51.GND
GND51: C52.2, D52.1, J52.1, R52.1, U52.GND
GND52: C53.2, D53.1, J53.1, R53.1, U53.GND
GND53: C54.2, D54.1, J54.1, R54.1, U54.GND
GND54: C55.2, D55.1, J55.1, R55.1, U55.GND
GND55: C56.2, D56.1, J56.1, R56.1, U56.GND
GND56: C57.2, D57.1, J57.1, R57.1, U57.GND
GND57: C58.2, D58.1, J58.1, R58.1, U58.GND
GND58: C59.2, D59.1, J59.1, R59.1, U59.GND
GND59: C60.2, D60.1, J60.1, R60.1, U60.GND
PIR_OUT: J1.2, R5.2, U1.OUT
PIR_OUT1: J2.2, R1.2, U2.OUT
PIR_OUT2: J3.2, R2.2, U3.OUT
PIR_OUT3: J4.2, R3.2, U4.OUT
PIR_OUT4: J5.2, R4.2, U5.OUT
PIR_OUT5: J6.2, R6.2, U6.OUT
PIR_OUT6: J7.2, R7.2, U7.OUT
PIR_OUT7: J8.2, R8.2, U8.OUT
PIR_OUT8: J9.2, R9.2, U9.OUT
PIR_OUT9: J10.2, R10.2, U10.OUT
PIR_OUT10: J11.2, R11.2, U11.OUT
PIR_OUT11: J12.2, R12.2, U12.OUT
PIR_OUT12: J13.2, R13.2, U13.OUT
PIR_OUT13: J14.2, R14.2, U14.OUT
PIR_OUT14: J15.2, R15.2, U15.OUT
PIR_OUT15: J16.2, R16.2, U16.OUT
PIR_OUT16: J17.2, R17.2, U17.OUT
PIR_OUT17: J18.2, R18.2, U18.OUT
PIR_OUT18: J19.2, R19.2, U19.OUT
PIR_OUT19: J20.2, R20.2, U20.OUT
PIR_OUT20: J21.2, R21.2, U21.OUT
PIR_OUT21: J22.2, R22.2, U22.OUT
PIR_OUT22: J23.2, R23.2, U23.OUT
PIR_OUT23: J24.2, R24.2, U24.OUT
PIR_OUT24: J25.2, R25.2, U25.OUT
PIR_OUT25: J26.2, R26.2, U26.OUT
PIR_OUT26: J27.2, R27.2, U27.OUT
PIR_OUT27: J28.2, R28.2, U28.OUT
PIR_OUT28: J29.2, R29.2, U29.OUT
PIR_OUT29: J30.2, R30.2, U30.OUT
PIR_OUT30: J31.2, R31.2, U31.OUT
PIR_OUT31: J32.2, R32.2, U32.OUT
PIR_OUT32: J33.2, R33.2, U33.OUT
PIR_OUT33: J34.2, R34.2, U34.OUT
PIR_OUT34: J35.2, R35.2, U35.OUT
PIR_OUT35: J36.2, R36.2, U36.OUT
PIR_OUT36: J37.2, R37.2, U37.OUT
PIR_OUT37: J38.2, R38.2, U38.OUT
PIR_OUT38: J39.2, R39.2, U39.OUT
PIR_OUT39: J40.2, R40.2, U40.OUT
PIR_OUT40: J41.2, R41.2, U41.OUT
PIR_OUT41: J42.2, R42.2, U42.OUT
PIR_OUT42: J43.2, R43.2, U43.OUT
PIR_OUT43: J44.2, R44.2, U44.OUT
PIR_OUT44: J45.2, R45.2, U45.OUT
PIR_OUT45: J46.2, R46.2, U46.OUT
PIR_OUT46: J47.2, R47.2, U47.OUT
PIR_OUT47: J48.2, R48.2, U48.OUT
PIR_OUT48: J49.2, R49.2, U49.OUT
PIR_OUT49: J50.2, R50.2, U50.OUT
PIR_OUT50: J51.2, R51.2, U51.OUT
PIR_OUT51: J52.2, R52.2, U52.OUT
PIR_OUT52: J53.2, R53.2, U53.OUT
PIR_OUT53: J54.2, R54.2, U54.OUT
PIR_OUT54: J55.2, R55.2, U55.OUT
PIR_OUT55: J56.2, R56.2, U56.OUT
PIR_OUT56: J57.2, R57.2, U57.OUT
PIR_OUT57: J58.2, R58.2, U58.OUT
PIR_OUT58: J59.2, R59.2, U59.OUT
PIR_OUT59: J60.2, R60.2, U60.OUT
